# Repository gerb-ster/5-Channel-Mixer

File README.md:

# 5 Channel Mixer

This one is not that special, it’s just a simple 5 channel mixer build around a TL074 and a TL072, very useful though.

## Status: Finished

- done: first schematic & board design
- done: breadboard and test
- done: design frontpanel
- done: order PCB and build prototype

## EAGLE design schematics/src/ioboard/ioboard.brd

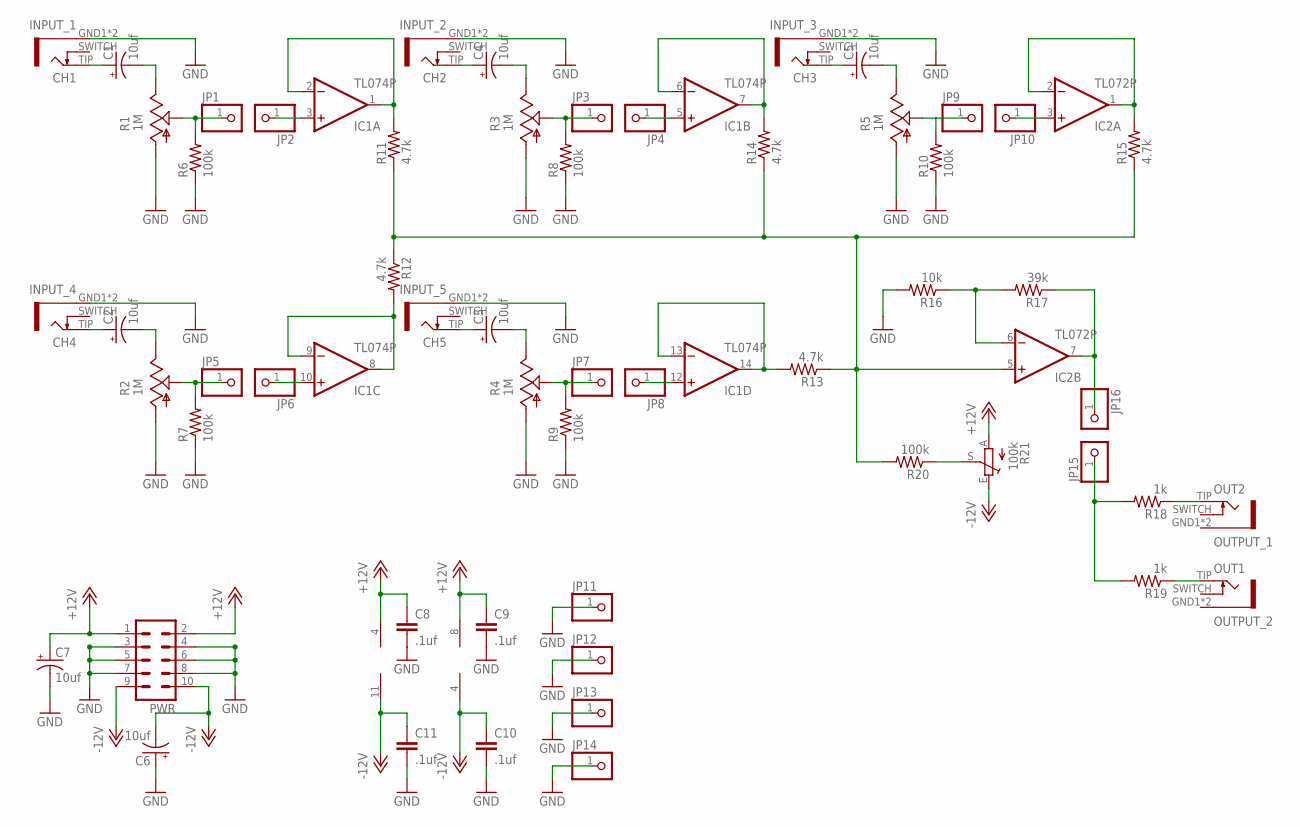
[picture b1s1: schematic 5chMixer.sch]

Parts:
C1, C2, C3, C4, C5, C6, C7: 10uf; E2,5-5
C8, C9, C10, C11: .1uf; C050-024X044
CH1: INPUT_1; PJ301BM
CH2: INPUT_2; PJ301BM
CH3: INPUT_3; PJ301BM
CH4: INPUT_4; PJ301BM
CH5: INPUT_5; PJ301BM
IC1: TL074P; DIL14
IC2: TL072P; DIL08
JP1, JP2, JP3, JP4, JP5, JP6, JP7, JP8, JP9, JP10, JP11, JP12, JP13, JP14, JP15, JP16: PINHD-1X1; 1X01
OUT1: OUTPUT_2; PJ301BM
OUT2: OUTPUT_1; PJ301BM
PWR: ML10
R1, R2, R3, R4, R5: 1M; EVUF
R6, R7, R8, R9, R10: 100k; 0204/7
R11, R12, R13, R14, R15: 4.7k; 0207/2V
R16: 10k; 0207/2V
R17: 39k; 0207/2V
R18, R19: 1k; 0204/7
R20: 100k; 0207/2V
R21: 100k; S64YW

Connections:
+12V: C7.+, C8.1, C9.1, IC1.4 (V+), IC2.8 (V+), PWR.1, PWR.2, R21.A
-12V: C6.-, C10.1, C11.1, IC1.11 (V-), IC2.4 (V-), PWR.9, PWR.10, R21.E
GND: C6.+, C7.-, C8.2, C9.2, C10.2, C11.2, CH1.GND1 (5), CH1.GND2 (5), CH2.GND1 (5), CH2.GND2 (5), CH3.GND1 (5), CH3.GND2 (5), CH4.GND1 (5), CH4.GND2 (5), CH5.GND1 (5), CH5.GND2 (5), JP11.1, JP12.1, JP13.1, JP14.1, PWR.3, PWR.4, PWR.5, PWR.6, PWR.7, PWR.8, R1.1 (A), R2.1 (A), R3.1 (A), R4.1 (A), R5.1 (A), R6.1, R7.1, R8.1, R9.1, R10.1, R16.2
unnamed: IC1.6 (-IN), IC1.7 (OUT), R14.2
unnamed: IC1.1 (OUT), IC1.2 (-IN), R11.2
unnamed: IC1.8 (OUT), IC1.9 (-IN), R12.2
unnamed: JP5.1, R2.2 (S), R7.2
unnamed: JP1.1, R1.2 (S), R6.2
unnamed: JP3.1, R3.2 (S), R8.2
unnamed: JP7.1, R4.2 (S), R9.2
unnamed: JP9.1, R5.2 (S), R10.2
unnamed: IC1.13 (-IN), IC1.14 (OUT), R13.2
unnamed: C1.+, CH1.TIP (3)
unnamed: C2.+, CH4.TIP (3)
unnamed: C4.+, CH2.TIP (3)
unnamed: C5.+, CH3.TIP (3)
unnamed: IC2.1 (OUT), IC2.2 (-IN), R15.2
unnamed: C1.-, R1.3 (E)
unnamed: C2.-, R2.3 (E)
unnamed: C4.-, R3.3 (E)
unnamed: C3.-, R4.3 (E)
unnamed: C3.+, CH5.TIP (3)
unnamed: IC2.5 (+IN), R11.1, R12.1, R13.1, R14.1, R15.1, R20.2
unnamed: IC1.3 (+IN), JP2.1
unnamed: IC1.5 (+IN), JP4.1
unnamed: JP15.1, R18.2, R19.2
unnamed: R20.1, R21.S
unnamed: C5.-, R5.3 (E)
unnamed: IC2.6 (-IN), R16.1, R17.2
unnamed: OUT2.TIP (3), R18.1
unnamed: OUT1.TIP (3), R19.1
unnamed: IC1.10 (+IN), JP6.1
unnamed: IC1.12 (+IN), JP8.1
unnamed: IC2.3 (+IN), JP10.1
unnamed: IC2.7 (OUT), JP16.1, R17.1

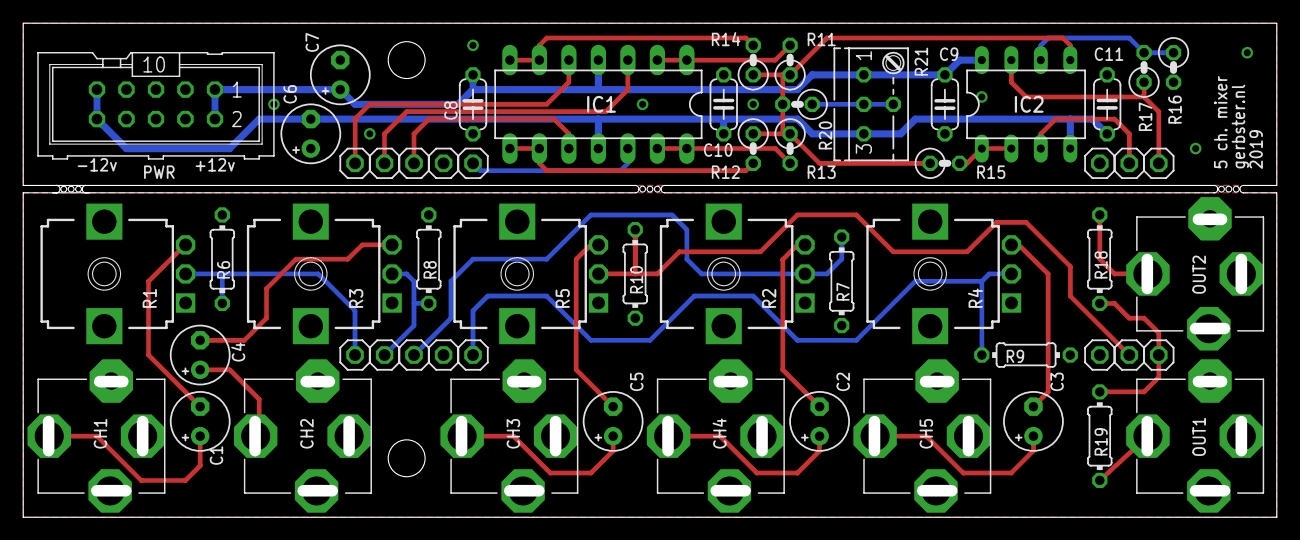
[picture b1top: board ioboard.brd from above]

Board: 2 copper layers, 108.0 x 42.5 mm, 58 parts (0 on the bottom side), 35 nets.

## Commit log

2021-05-06 some files
2021-05-07 Added files & structure
2021-05-10 Added Status
2021-05-11 Added Status & Images
2021-08-06 Updated some schematics and docs
2021-08-10 Fixed some bugs and updated documentation
2022-04-20 Some updates & bugfixes
2022-04-22 Fixed schematics & descriptions
2022-05-17 Updated Firmware
2022-05-18 Updated Faceplates
2022-05-18 Fixed issues
2022-05-21 Fixed schematics
2022-05-28 General updates
